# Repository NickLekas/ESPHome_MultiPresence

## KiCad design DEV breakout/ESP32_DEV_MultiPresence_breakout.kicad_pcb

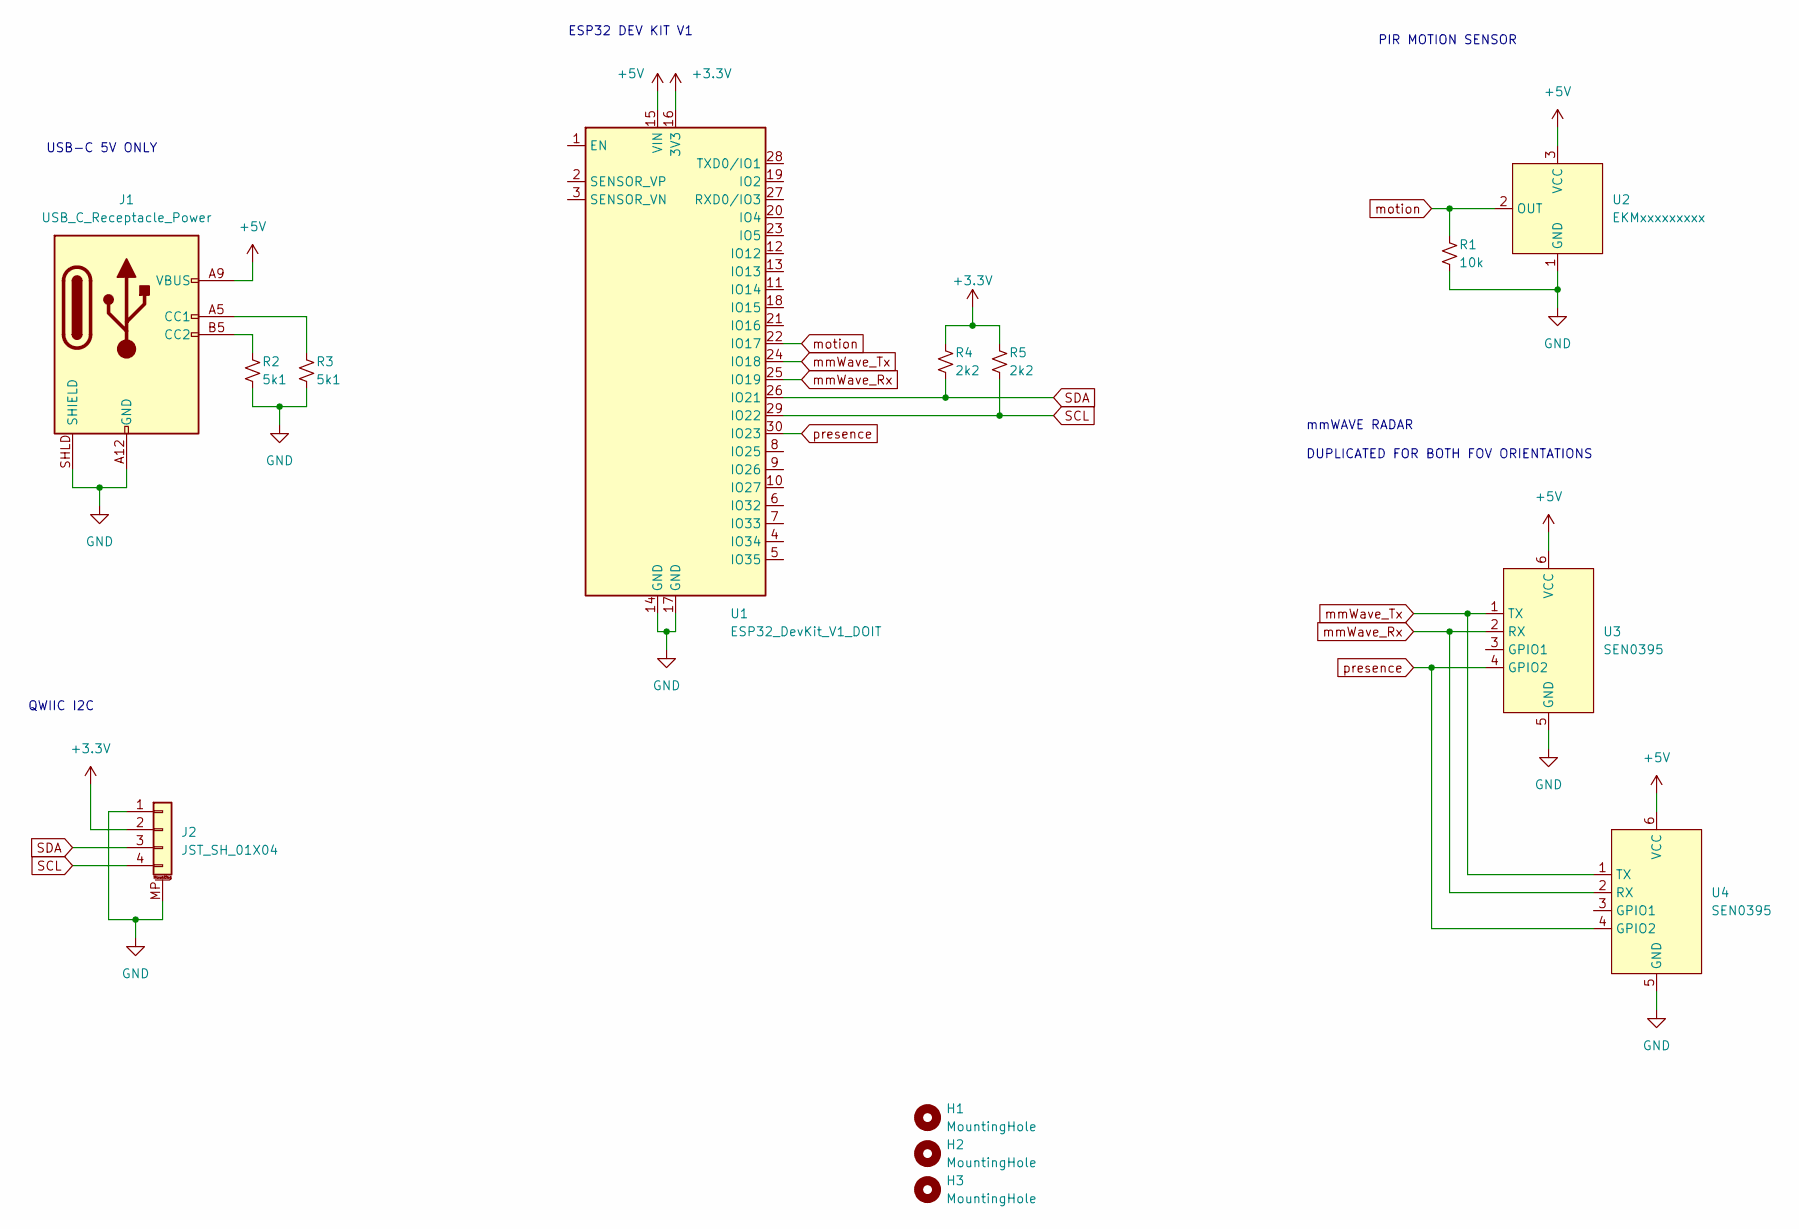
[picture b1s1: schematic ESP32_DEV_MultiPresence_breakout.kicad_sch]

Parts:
H1, H2, H3: MountingHole; MountingHole_3.2mm_M3
J1: USB_C_Receptacle_Power; USB_C_Power
J2: JST_SH_01X04; JST_SH_SM04B-SRSS-TB_1x04-1MP_P1.00mm_Horizontal
R1: 10k; R_0603_1608Metric
R2, R3: 5k1; R_0603_1608Metric
R4, R5: 2k2; R_0603_1608Metric
U1: ESP32_DevKit_V1_DOIT; esp32_devkit_v1
U2: EKMxxxxxxxxx
U3, U4: SEN0395

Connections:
+3V3: J2.2, R4.1, R5.1, U1.16 (3V3)
+5V: J1.A9 (VBUS), J1.B9 (VBUS), U1.15 (VIN), U2.3 (VCC), U3.6 (VCC), U4.6 (VCC)
GND: J1.A12 (GND), J1.B12 (GND), J1.SHLD (SHIELD), J2.1, J2.MP (MountPin), R1.2, R2.2, R3.2, U1.14 (GND), U1.17 (GND), U2.1 (GND), U3.5 (GND), U4.5 (GND)
unnamed: J1.A5 (CC1), R3.1
unnamed: J1.B5 (CC2), R2.1
SCL: J2.4, R5.2, U1.29 (IO22)
SDA: J2.3, R4.2, U1.26 (IO21)
mmWave_Rx: U1.25 (IO19), U3.2 (RX), U4.2 (RX)
mmWave_Tx: U1.24 (IO18), U3.1 (TX), U4.1 (TX)
motion: R1.1, U1.22 (IO17), U2.2 (OUT)
presence: U1.30 (IO23), U3.4 (GPIO2), U4.4 (GPIO2)

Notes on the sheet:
mmWAVE RADAR DUPLICATED FOR BOTH FOV ORIENTATIONS
PIR MOTION SENSOR
USB-C 5V ONLY
ESP32 DEV KIT V1
QWIIC I2C

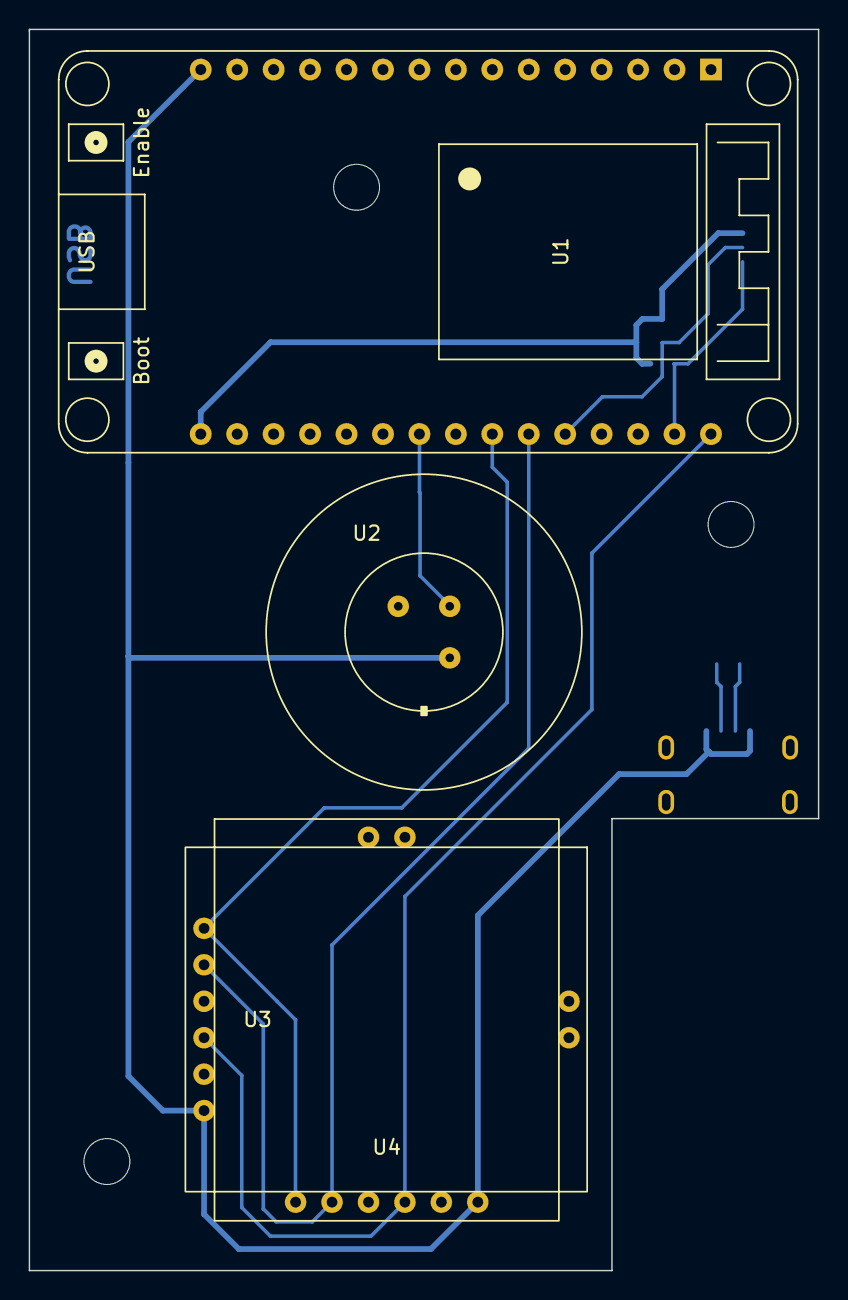
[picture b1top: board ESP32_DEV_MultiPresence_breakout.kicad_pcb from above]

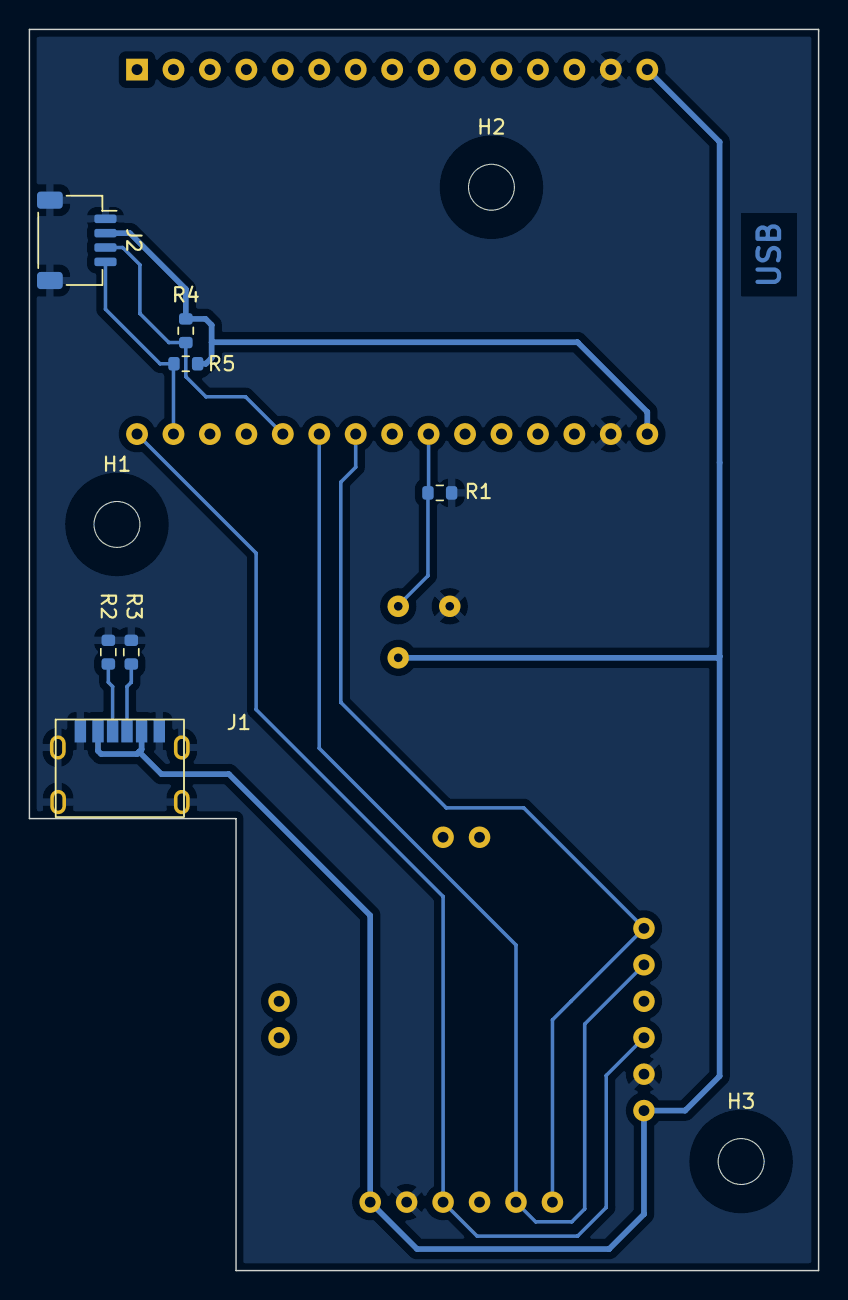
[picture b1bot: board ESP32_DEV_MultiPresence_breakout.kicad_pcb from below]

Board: 2 copper layers, 55.0 x 86.5 mm, 14 parts (10 on the bottom side), 11 nets.

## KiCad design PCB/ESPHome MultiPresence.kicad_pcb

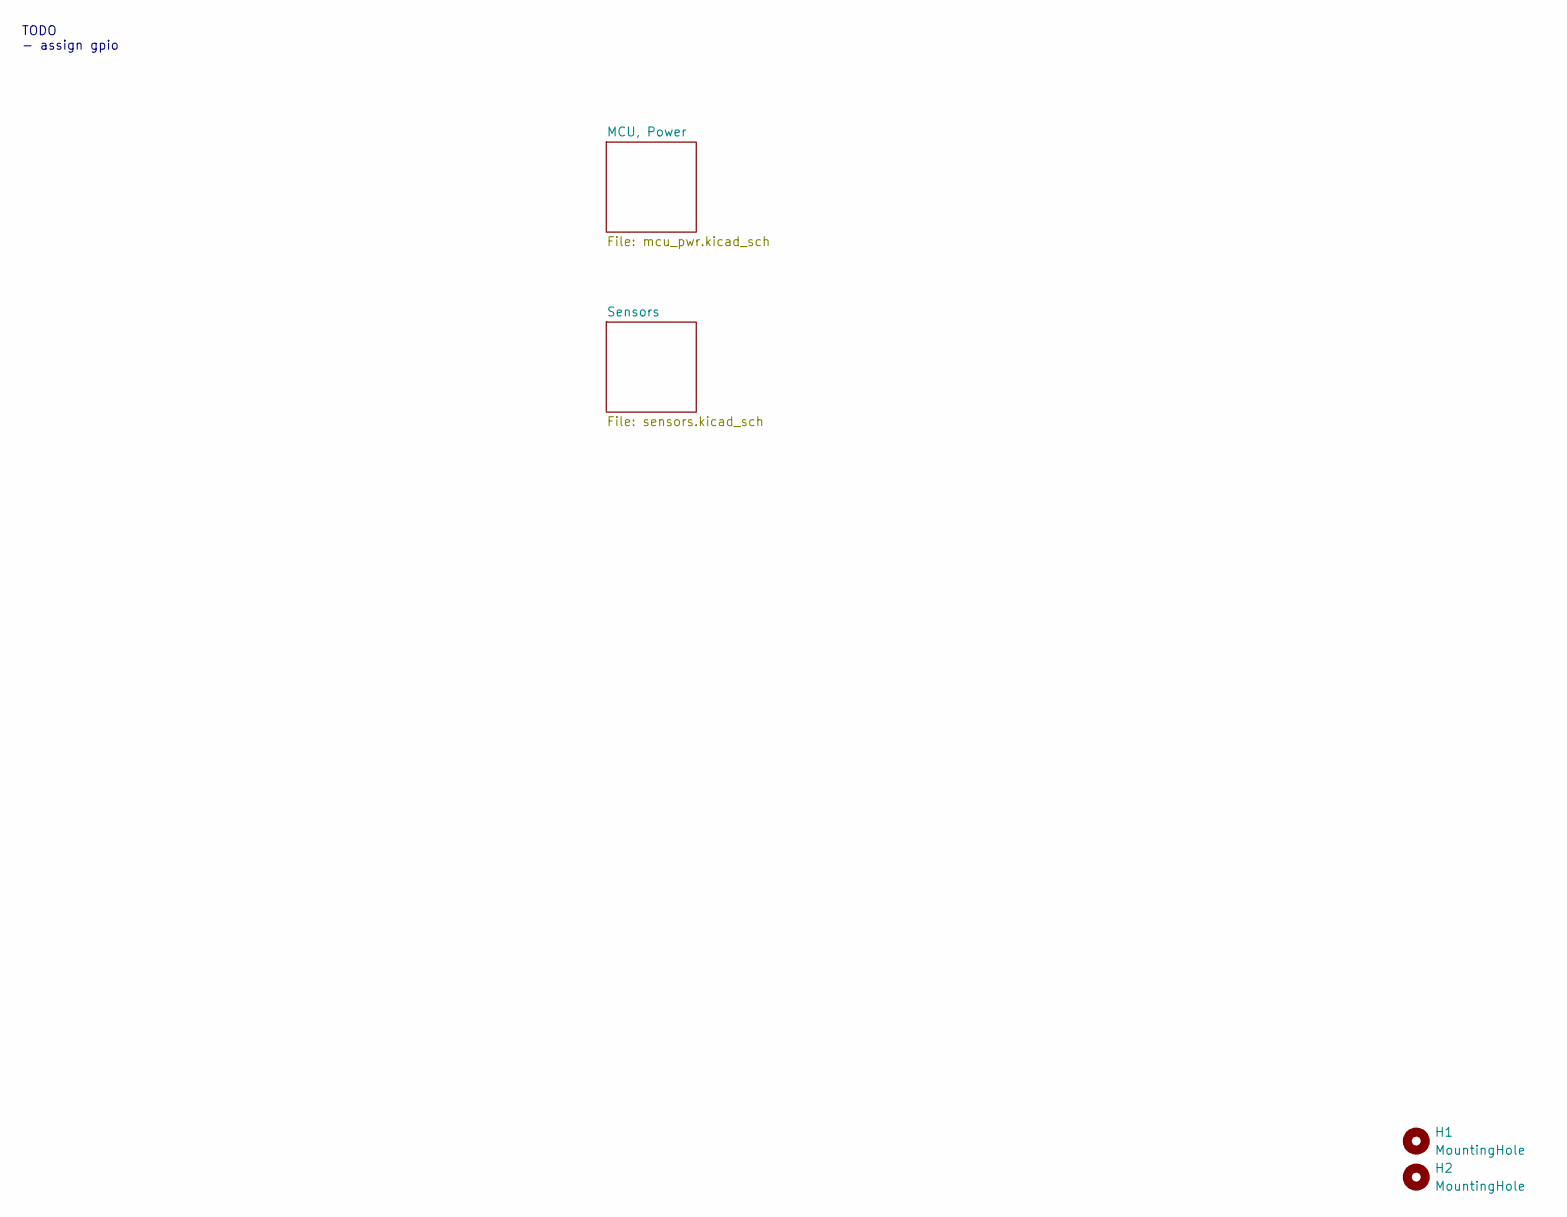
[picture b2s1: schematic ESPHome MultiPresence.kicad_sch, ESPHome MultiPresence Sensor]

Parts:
H1, H2: MountingHole; MountingHole_3.2mm_M3_Pad_Via

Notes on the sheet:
TODO - assign gpio

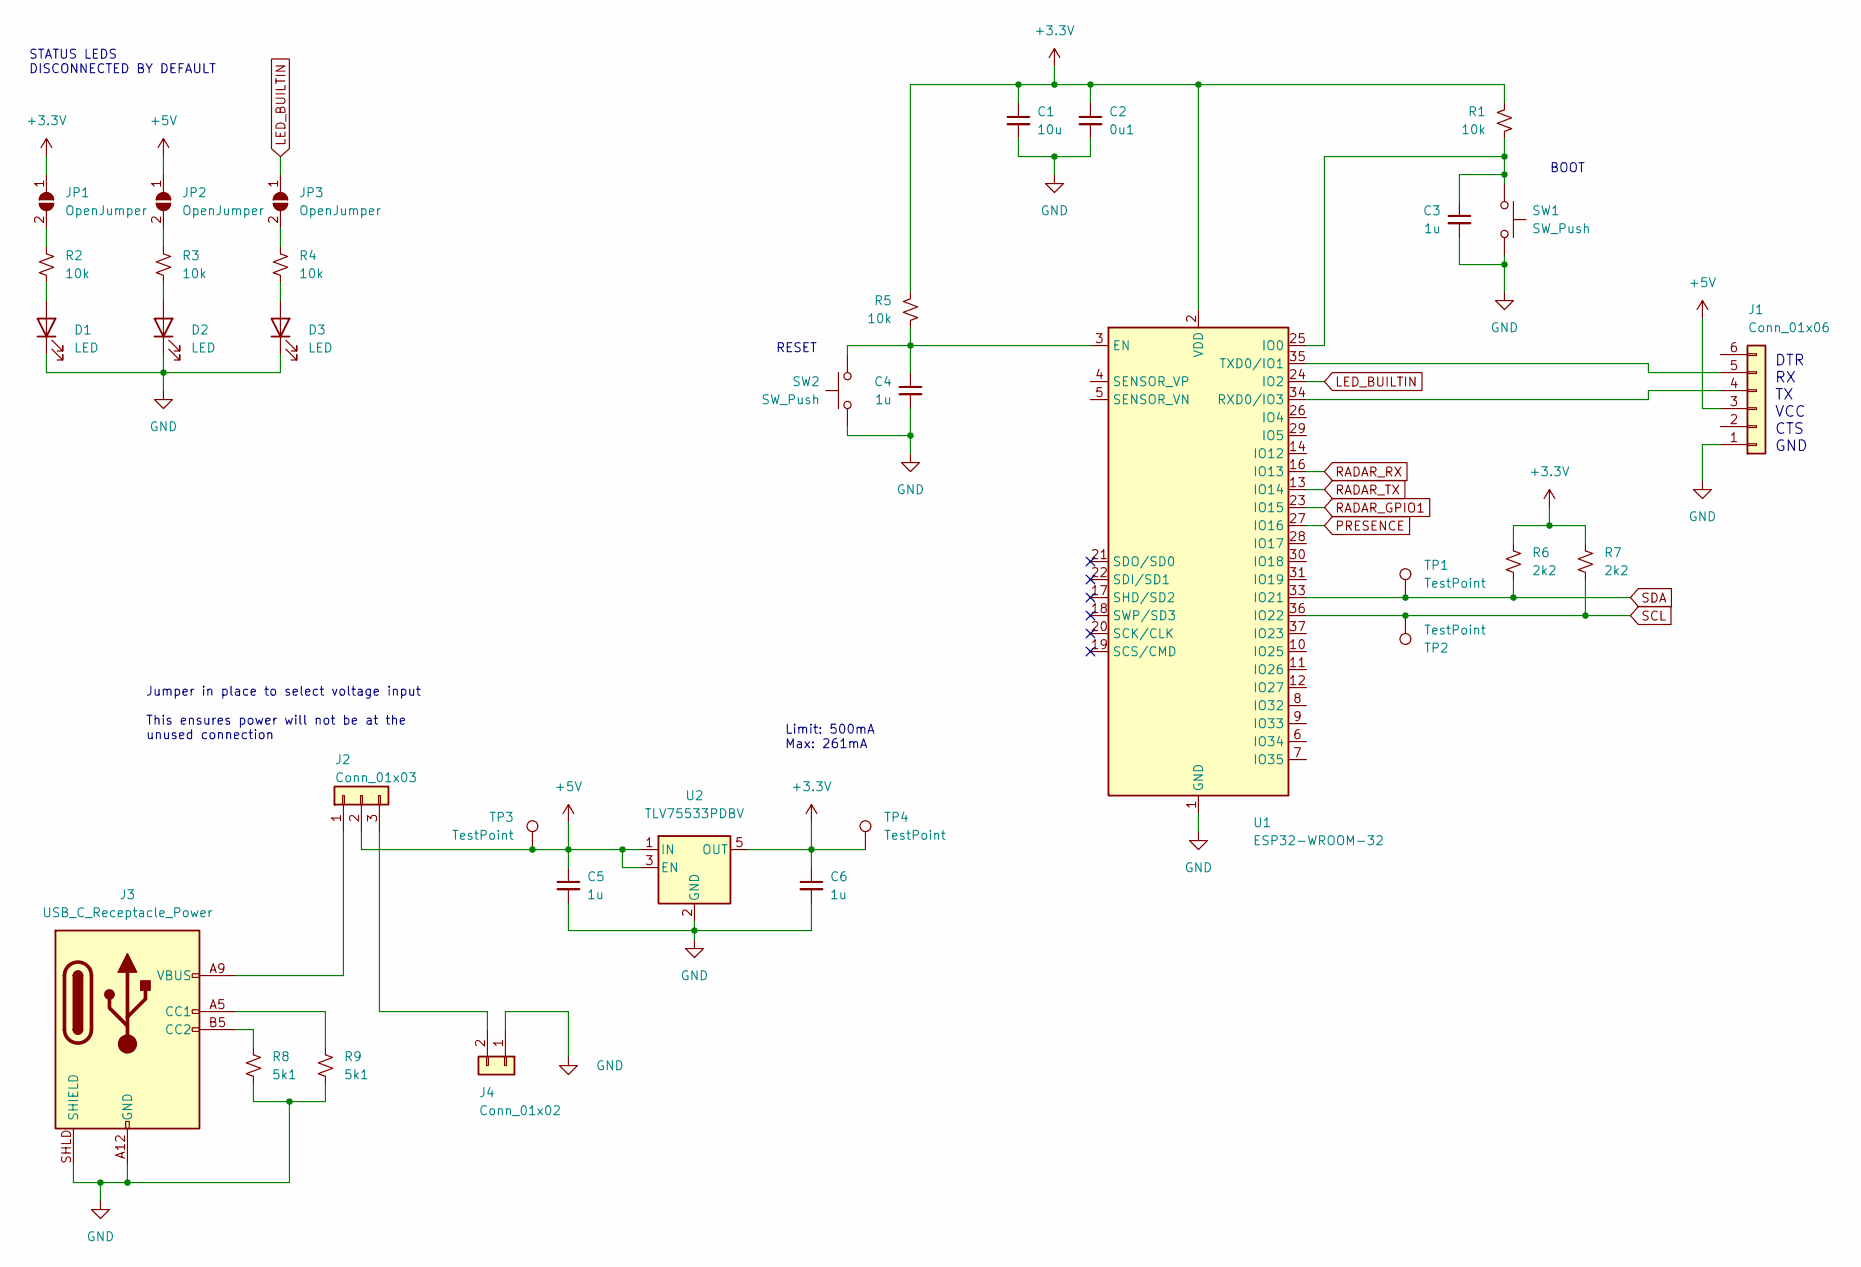
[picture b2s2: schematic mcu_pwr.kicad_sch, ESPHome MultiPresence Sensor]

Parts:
C1: 10u; R_0603_1608Metric
C2: 0u1; R_0603_1608Metric
C3, C4, C5, C6: 1u; R_0603_1608Metric
D1, D2, D3: LED; D_0603_1608Metric
J1: Conn_01x06; PinHeader_1x06_P2.54mm_Vertical
J2: Conn_01x03; PinHeader_1x03_P2.54mm_Vertical
J3: USB_C_Receptacle_Power; USB_C_Power
J4: Conn_01x02; PinHeader_1x02_P2.54mm_Vertical
JP1, JP2, JP3: OpenJumper; SolderJumper-2_P1.3mm_Open_TrianglePad1.0x1.5mm
R1, R2, R3, R4, R5: 10k; R_0603_1608Metric
R6, R7: 2k2; R_0603_1608Metric
R8, R9: 5k1; R_0603_1608Metric
SW1, SW2: SW_Push; SW_SPST_EVQP2
TP1, TP2, TP3, TP4: TestPoint; TestPoint_THTPad_2.0x2.0mm_Drill1.0mm
U1: ESP32-WROOM-32
U2: TLV75533PDBV; SOT-23-5

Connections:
+3.3V: C1.1, C2.1, C6.1, JP1.1 (A), R1.1, R5.1, R6.1, R7.1, TP4.1, U1.2 (VDD), U2.5 (OUT); also elsewhere on the board
+5V: C5.1, J1.3, J2.2, JP2.1 (A), TP3.1, U2.1 (IN), U2.3 (EN); also elsewhere on the board
GND: C1.2, C2.2, C3.2, C4.2, C5.2, C6.2, D1.1 (K), D2.1 (K), D3.1 (K), J1.1, J3.A12 (GND), J3.B12 (GND), J3.SHLD (SHIELD), J4.1, R8.2, R9.2, SW1.2, SW2.2, U1.1 (GND), U1.15 (GND), U1.38 (GND), U1.39 (GND), U2.2 (GND); also elsewhere on the board
LED_BUILTIN: JP3.1 (A), U1.24 (IO2)
unnamed: C3.1, R1.2, SW1.1, U1.25 (IO0)
unnamed: C4.1, R5.2, SW2.1, U1.3 (EN)
unnamed: D1.2 (A), R2.2
unnamed: D2.2 (A), R3.2
unnamed: D3.2 (A), R4.2
unnamed: J1.4, U1.34 (RXD0/IO3)
unnamed: J1.5, U1.35 (TXD0/IO1)
unnamed: J2.1, J3.A9 (VBUS), J3.B9 (VBUS)
unnamed: J2.3, J4.2
unnamed: J3.A5 (CC1), R9.1
unnamed: J3.B5 (CC2), R8.1
unnamed: JP1.2 (B), R2.1
unnamed: JP2.2 (B), R3.1
unnamed: JP3.2 (B), R4.1
PRESENCE: U1.27 (IO16); also elsewhere on the board
RADAR_GPIO1: U1.23 (IO15); also elsewhere on the board
RADAR_RX: U1.16 (IO13); also elsewhere on the board
RADAR_TX: U1.13 (IO14); also elsewhere on the board
SCL: R7.2, TP2.1, U1.36 (IO22); also elsewhere on the board
SDA: R6.2, TP1.1, U1.33 (IO21); also elsewhere on the board

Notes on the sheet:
RESET
BOOT
Jumper in place to select voltage input This ensures power will not be at the unused connection
STATUS LEDS DISCONNECTED BY DEFAULT
DTR RX TX VCC CTS GND
Limit: 500mA Max: 261mA

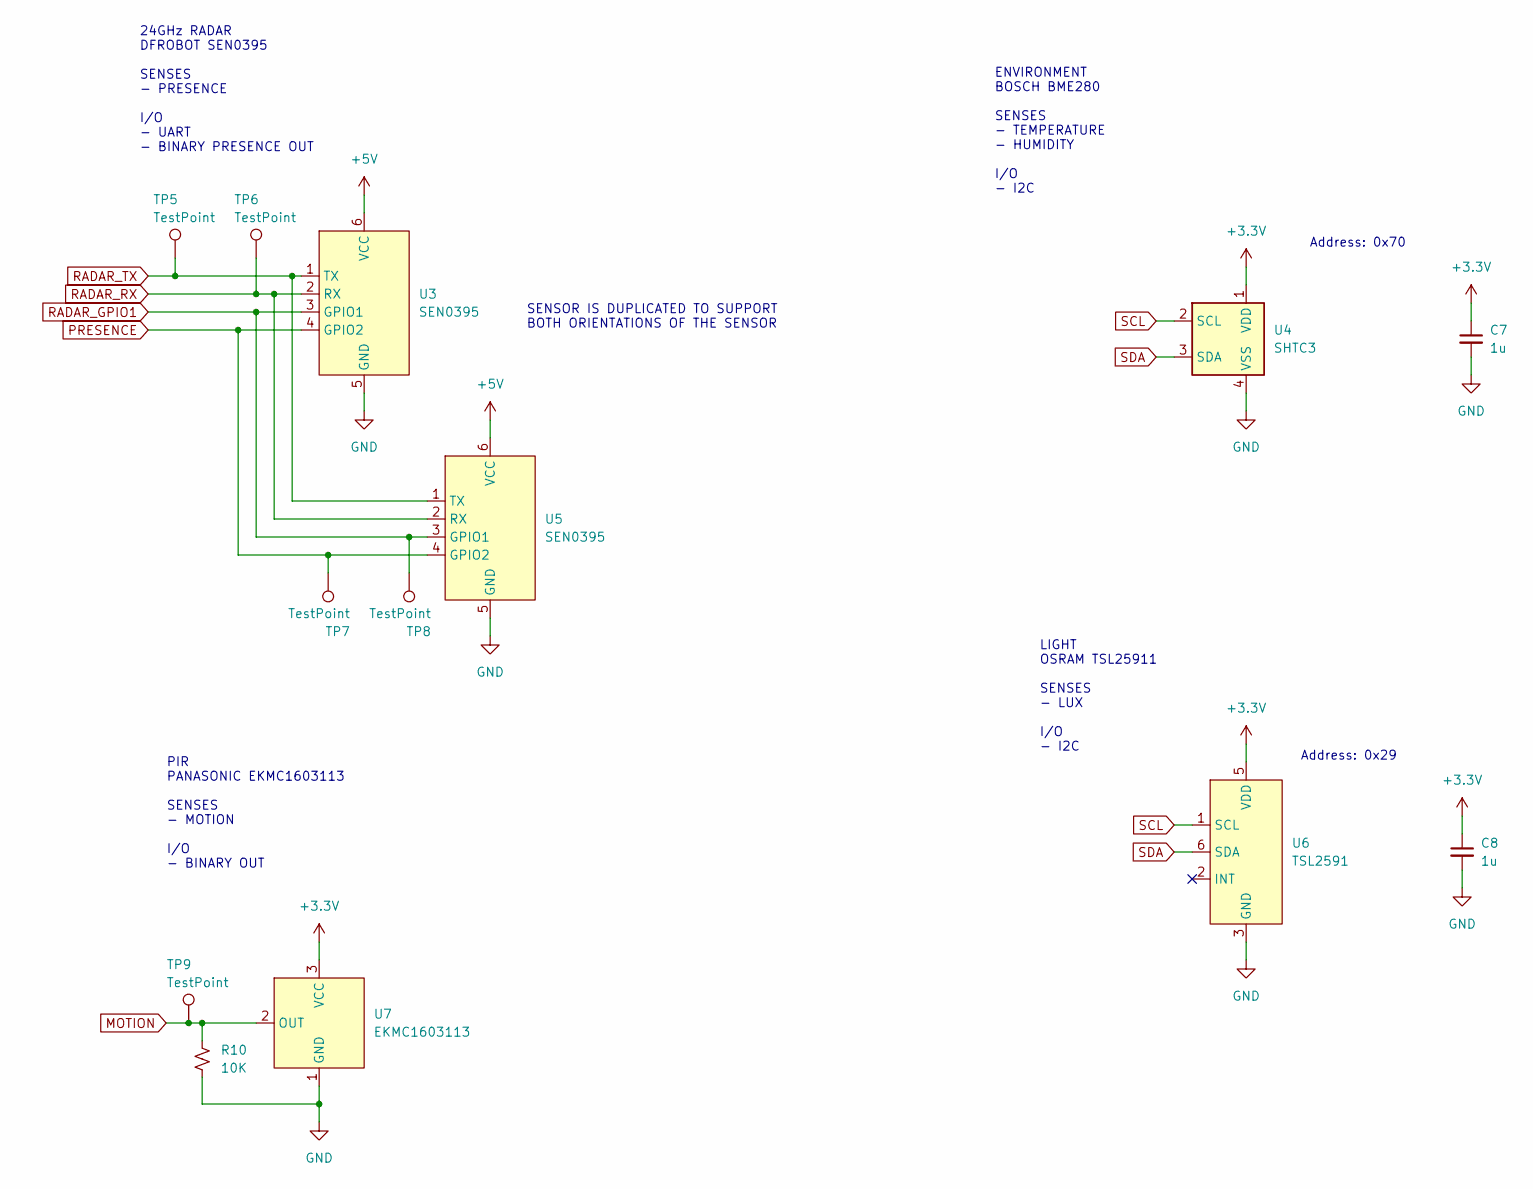
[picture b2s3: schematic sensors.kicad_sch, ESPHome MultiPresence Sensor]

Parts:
C7, C8: 1u; R_0603_1608Metric
R10: 10K; R_0603_1608Metric
TP5, TP6, TP7, TP8, TP9: TestPoint; TestPoint_THTPad_2.0x2.0mm_Drill1.0mm
U3, U5: SEN0395
U4: SHTC3; Sensirion_DFN-4-1EP_2x2mm_P1mm_EP0.7x1.6mm
U6: TSL2591; ODFN-6
U7: EKMC1603113; EKMxxxxxxxxx

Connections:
+3.3V: C7.1, C8.1, U4.1 (VDD), U6.5 (VDD), U7.3 (VCC); also elsewhere on the board
+5V: U3.6 (VCC), U5.6 (VCC); also elsewhere on the board
GND: C7.2, C8.2, R10.2, U3.5 (GND), U4.4 (VSS), U4.5 (VSS), U5.5 (GND), U6.3 (GND), U7.1 (GND); also elsewhere on the board
MOTION: R10.1, TP9.1, U7.2 (OUT)
PRESENCE: TP7.1, U3.4 (GPIO2), U5.4 (GPIO2); also elsewhere on the board
RADAR_GPIO1: TP8.1, U3.3 (GPIO1), U5.3 (GPIO1); also elsewhere on the board
RADAR_RX: TP6.1, U3.2 (RX), U5.2 (RX); also elsewhere on the board
RADAR_TX: TP5.1, U3.1 (TX), U5.1 (TX); also elsewhere on the board
SCL: U4.2 (SCL), U6.1 (SCL); also elsewhere on the board
SDA: U4.3 (SDA), U6.6 (SDA); also elsewhere on the board

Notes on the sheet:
PIR PANASONIC EKMC1603113 SENSES - MOTION I/O - BINARY OUT
Address: 0x70
ENVIRONMENT BOSCH BME280 SENSES - TEMPERATURE - HUMIDITY I/O - I2C
24GHz RADAR DFROBOT SEN0395 SENSES - PRESENCE I/O - UART - BINARY PRESENCE OUT
Address: 0x29
LIGHT OSRAM TSL25911 SENSES - LUX I/O - I2C
SENSOR IS DUPLICATED TO SUPPORT BOTH ORIENTATIONS OF THE SENSOR

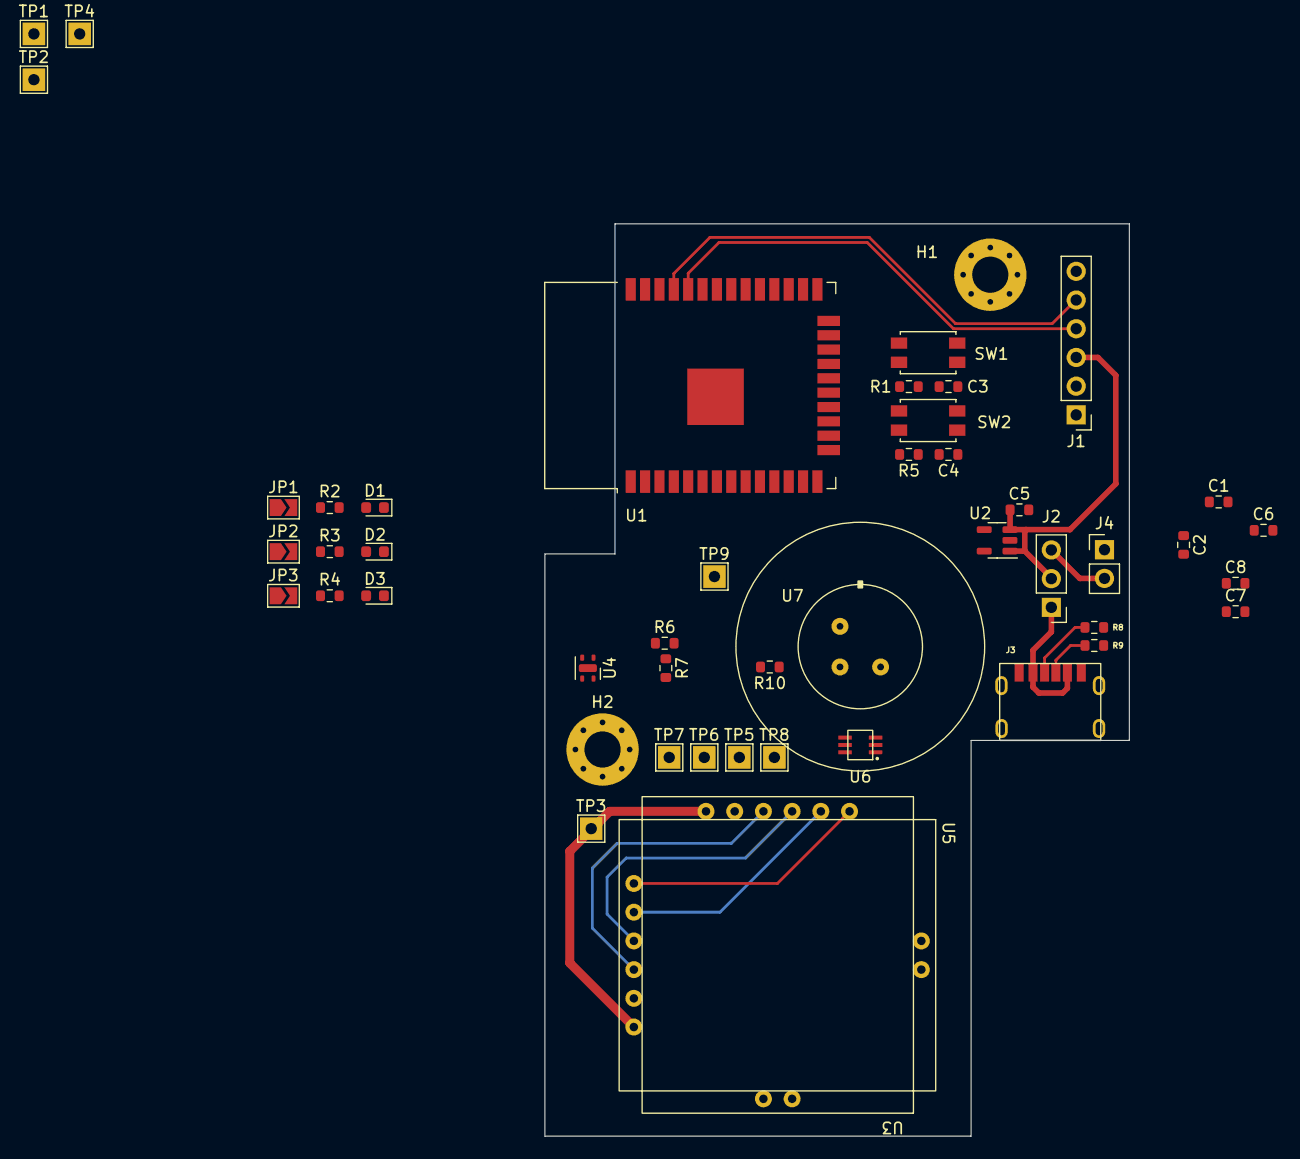
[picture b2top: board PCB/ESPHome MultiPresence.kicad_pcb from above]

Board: 2 copper layers, 51.7 x 80.7 mm, 48 parts (0 on the bottom side), 25 nets.

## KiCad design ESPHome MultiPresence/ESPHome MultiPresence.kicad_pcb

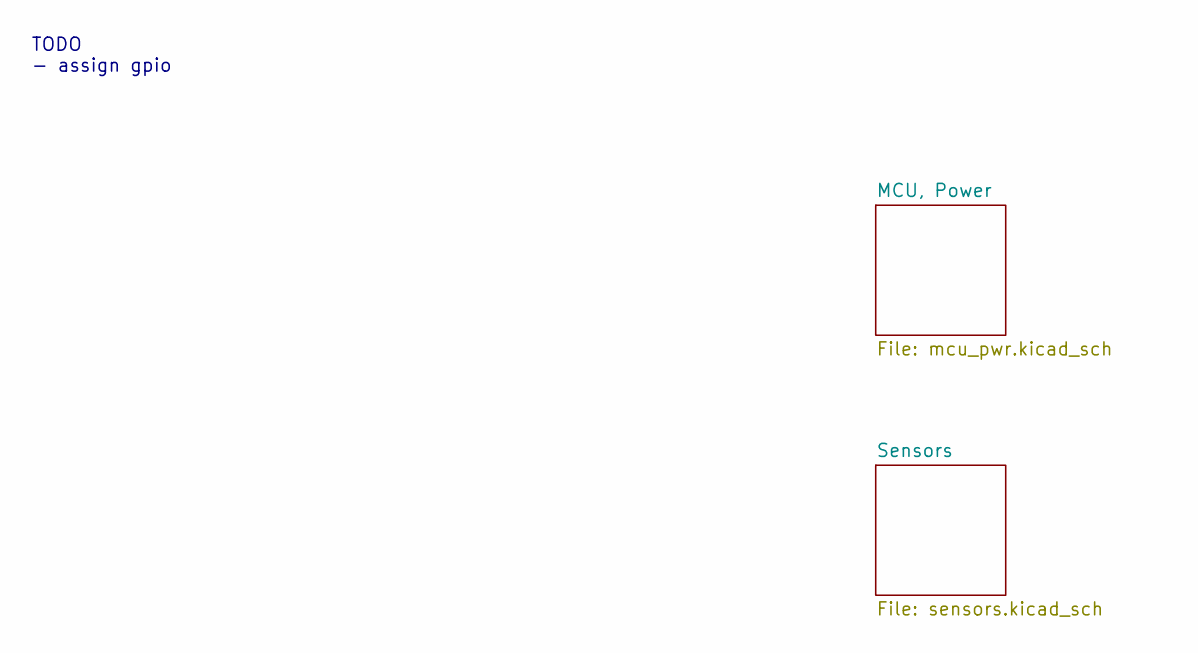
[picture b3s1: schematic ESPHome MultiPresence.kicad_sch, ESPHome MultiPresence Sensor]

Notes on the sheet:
TODO - assign gpio

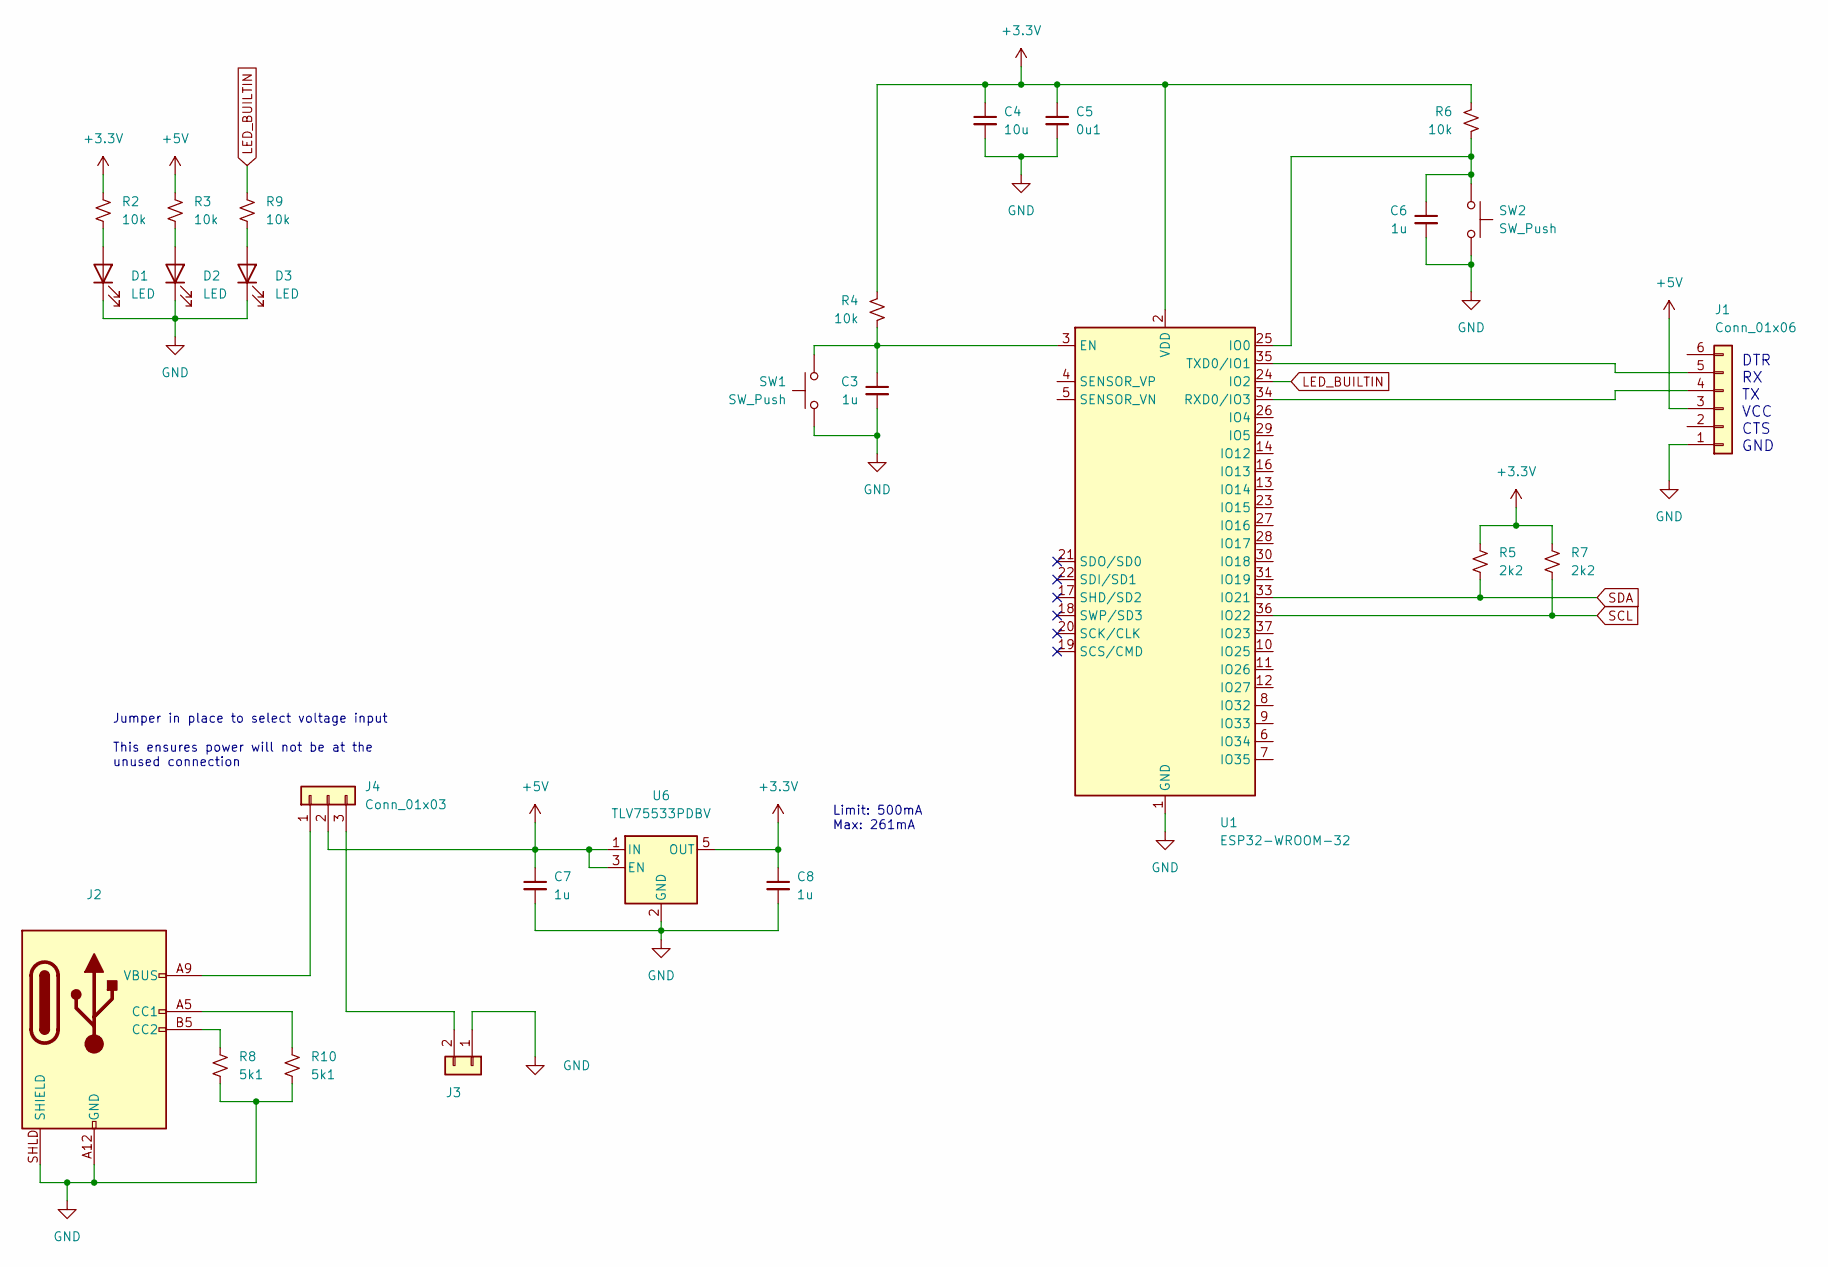
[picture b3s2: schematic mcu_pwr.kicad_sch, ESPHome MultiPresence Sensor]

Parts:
C3, C6, C7, C8: 1u; R_0603_1608Metric
C4: 10u; R_0603_1608Metric
C5: 0u1; R_0603_1608Metric
D1, D2, D3: LED; D_0603_1608Metric
J1: Conn_01x06; PinHeader_1x06_P2.54mm_Vertical
J2, J3: (no value)
J4: Conn_01x03; PinHeader_1x03_P2.54mm_Vertical
R2, R3, R4, R6, R9: 10k; R_0603_1608Metric
R5, R7: 2k2; R_0603_1608Metric
R8, R10: 5k1; R_0603_1608Metric
SW1, SW2: SW_Push; SW_SPST_EVQP2
U1: ESP32-WROOM-32
U6: TLV75533PDBV; SOT-23-5

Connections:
+3.3V: C4.1, C5.1, C8.1, R2.1, R4.1, R5.1, R6.1, R7.1, U1.2 (VDD), U6.5 (OUT); also elsewhere on the board
+5V: C7.1, J1.3, J4.2, R3.1, U6.1 (IN), U6.3 (EN); also elsewhere on the board
GND: C3.2, C4.2, C5.2, C6.2, C7.2, C8.2, D1.1 (K), D2.1 (K), D3.1 (K), J1.1, J2.A12 (GND), J2.B12 (GND), J2.SHLD (SHIELD), J3.1, R8.2, R10.2, SW1.2, SW2.2, U1.1 (GND), U1.15 (GND), U1.38 (GND), U1.39 (GND), U6.2 (GND); also elsewhere on the board
LED_BUILTIN: R9.1, U1.24 (IO2)
unnamed: C3.1, R4.2, SW1.1, U1.3 (EN)
unnamed: C6.1, R6.2, SW2.1, U1.25 (IO0)
unnamed: D1.2 (A), R2.2
unnamed: D2.2 (A), R3.2
unnamed: D3.2 (A), R9.2
unnamed: J1.4, U1.34 (RXD0/IO3)
unnamed: J1.5, U1.35 (TXD0/IO1)
unnamed: J2.A5 (CC1), R10.1
unnamed: J2.A9 (VBUS), J2.B9 (VBUS), J4.1
unnamed: J2.B5 (CC2), R8.1
unnamed: J3.2, J4.3
SCL: R7.2, U1.36 (IO22); also elsewhere on the board
SDA: R5.2, U1.33 (IO21); also elsewhere on the board

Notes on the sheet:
Jumper in place to select voltage input This ensures power will not be at the unused connection
DTR RX TX VCC CTS GND
Limit: 500mA Max: 261mA

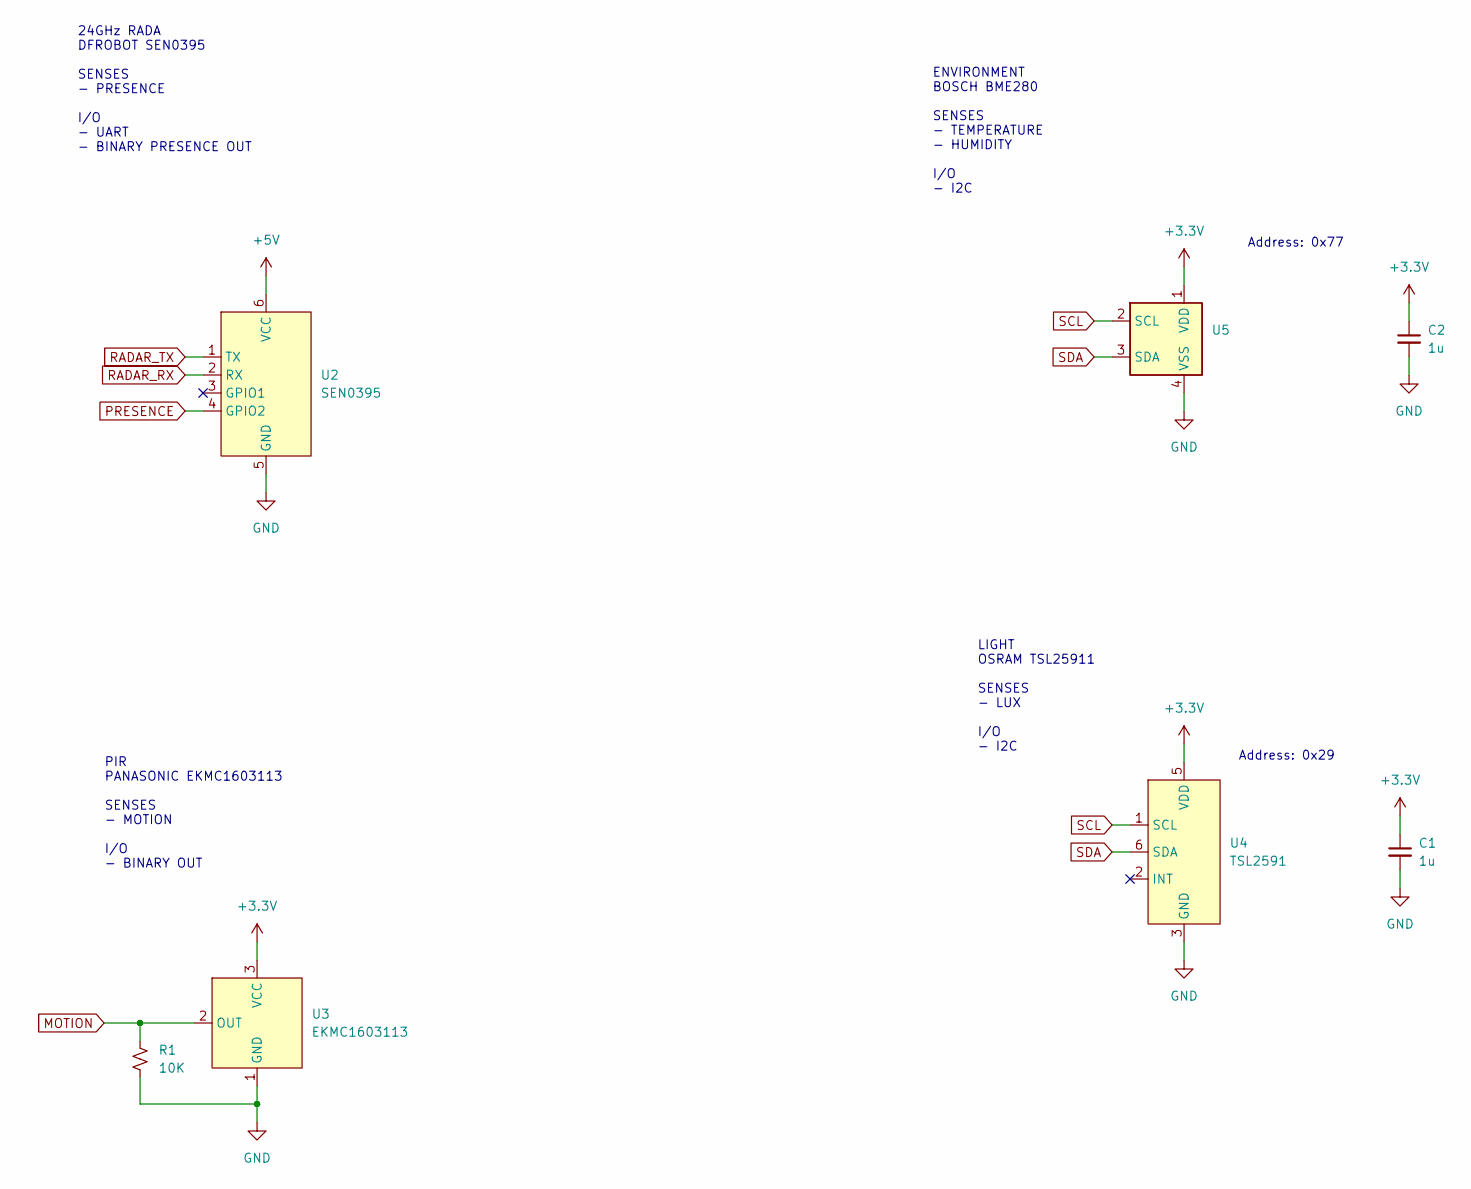
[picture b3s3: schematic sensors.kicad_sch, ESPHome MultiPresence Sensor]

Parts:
C1, C2: 1u; R_0603_1608Metric
R1: 10K; R_0603_1608Metric
U2: SEN0395
U3: EKMC1603113; EKMxxxxxxxxx
U4: TSL2591; ODFN-6
U5: (no value)

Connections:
+3.3V: C1.1, C2.1, U3.3 (VCC), U4.5 (VDD), U5.1 (VDD); also elsewhere on the board
+5V: U2.6 (VCC); also elsewhere on the board
GND: C1.2, C2.2, R1.2, U2.5 (GND), U3.1 (GND), U4.3 (GND), U5.4 (VSS); also elsewhere on the board
MOTION: R1.1, U3.2 (OUT)
PRESENCE: U2.4 (GPIO2)
RADAR_RX: U2.2 (RX)
RADAR_TX: U2.1 (TX)
SCL: U4.1 (SCL), U5.2 (SCL); also elsewhere on the board
SDA: U4.6 (SDA), U5.3 (SDA); also elsewhere on the board

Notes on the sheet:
PIR PANASONIC EKMC1603113 SENSES - MOTION I/O - BINARY OUT
Address: 0x77
ENVIRONMENT BOSCH BME280 SENSES - TEMPERATURE - HUMIDITY I/O - I2C
24GHz RADA DFROBOT SEN0395 SENSES - PRESENCE I/O - UART - BINARY PRESENCE OUT
Address: 0x29
LIGHT OSRAM TSL25911 SENSES - LUX I/O - I2C

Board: 2 copper layers, 33 parts (0 on the bottom side), 18 nets, no tracks yet.

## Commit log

2022-10-09 KiCad initial commit
2022-10-09 split schematic into 2 sheets, assigned all but J3 and SW3 footprints, started pcb layout
2022-10-09 small schematic changes
2022-10-09 added gitignore
2022-10-09 changed voltage switch to jumpper, changed screw terminal jst-ph
2022-10-10 removed depricated schematics, replaced BME280 with cheaper SHTC3
2022-10-10 replaced J3 with pinheadder, fixed USB-C footprint pin assignment
2022-10-11 Moved kicad files to the PCB folder
2022-10-17 updated footprints and started board layout
2022-10-19 board layout work
2022-11-05 added and laid out what can be a single sidded board for testing
2022-11-05 added a qwiic comptable connector for furure testing of I2C sensors from adafruit or sparkfun
2022-11-07 developed a single sidded board to accomodate the radar, pir, and esp32 dev kit v1
2022-11-07 moved 5V line to let more GND thermal connections on the radar
2022-11-07 added documentation to the schematic
2022-11-08 adjusted pir signal trace for nicer routing though the pull down
